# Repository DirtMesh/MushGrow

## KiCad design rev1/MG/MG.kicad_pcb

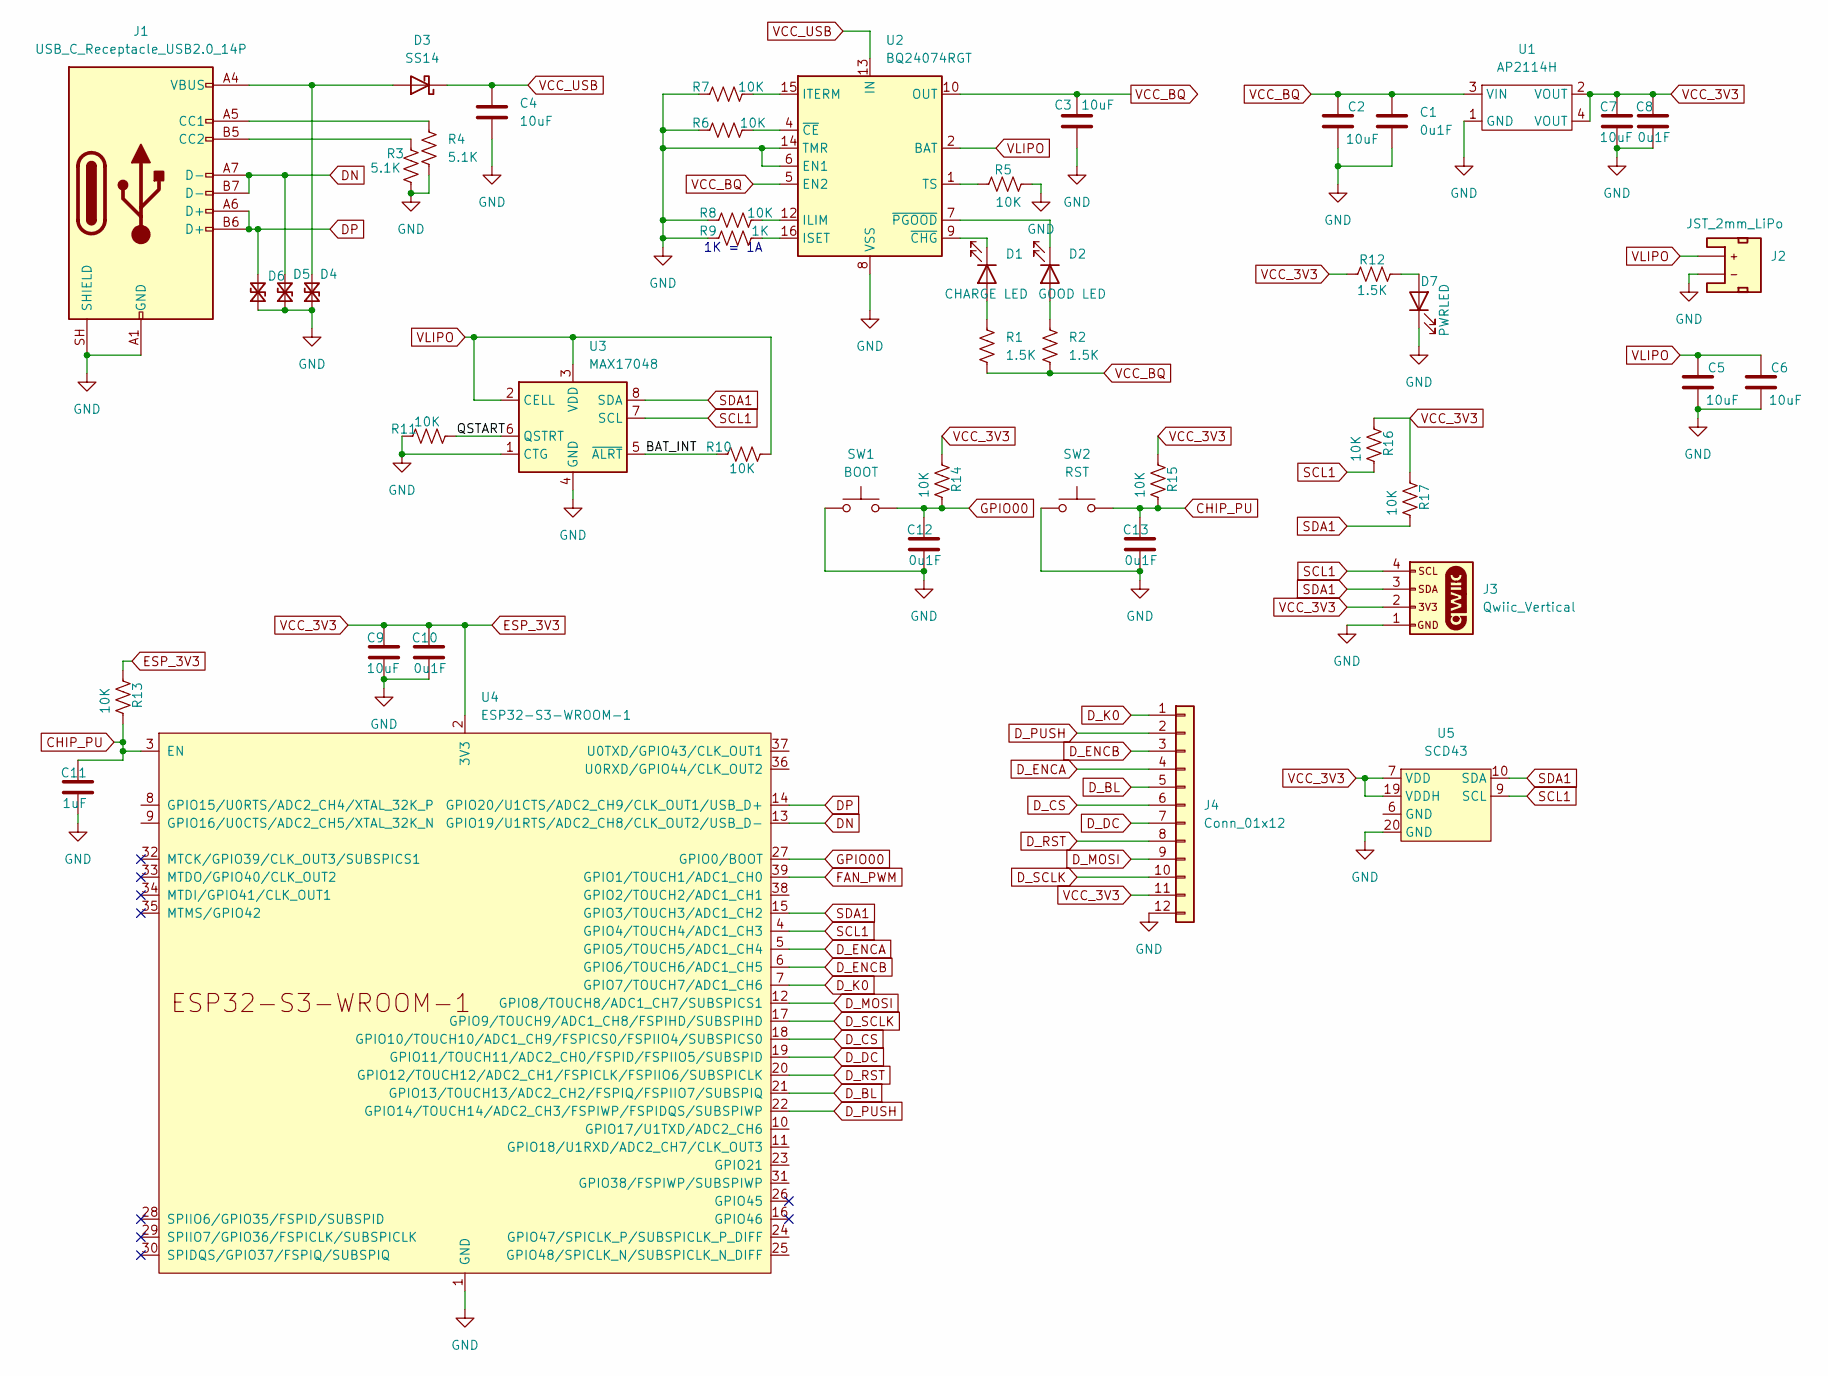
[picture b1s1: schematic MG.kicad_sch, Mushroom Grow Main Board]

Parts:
C1, C8, C10, C12, C13: 0u1F; C_0603_1608Metric
C2, C3, C4, C5, C6, C7, C9: 10uF; C_1206_3216Metric
C11: 1uF; C_0603_1608Metric
D1: CHARGE LED; LED_0603_1608Metric
D2: GOOD LED; LED_0603_1608Metric
D3: SS14; D_SMA
D4, D5, D6: TPD1E10B06DYAR; D_SOD-523
D7: PWRLED; LED_0603_1608Metric
J1: USB_C_Receptacle_USB2.0_14P; USB_C_Receptacle_GCT_USB4085
J2: JST_2mm_LiPo; JST_1x02_P2.0mm_Horizontal_SMD
J3: Qwiic_Vertical; JST_1x04_P1.0mm_Vertical_SMD
J4: Conn_01x12; JST_1x12_P1.0mm_Horizontal_SMD
R1, R2, R12: 1.5K; R_0603_1608Metric
R3, R4: 5.1K; R_0603_1608Metric
R5, R6, R7, R8, R10, R11, R13, R14, R15, R16, R17: 10K; R_0603_1608Metric
R9: 1K; R_0603_1608Metric
SW1: BOOT; Push_SMD_4.6x2.8mm_h1.9mm
SW2: RST; Push_SMD_4.6x2.8mm_h1.9mm
U1: AP2114H; SOT-223
U2: BQ24074RGT; VQFN-16-1EP_3x3mm_P0.5mm_EP1.6x1.6mm
U3: MAX17048; DFN-8_2x2mm_P0.5mm_EP1.2x0.8mm
U4: ESP32-S3-WROOM-1
U5: SCD43; Sensirion_SCD4x-1EP_10.1x10.1mm_P1.25mm_EP4.8x4.8mm

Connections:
/BAT_INT: R10.1, U3.5 (~ALRT)
/QSTART: R11.2, U3.6 (QSTRT)
CHIP_PU: C11.1, C13.1, R13.2, R15.2, SW2.2, U4.3 (EN)
DN: D5.2 (A2), J1.A7 (D-), J1.B7 (D-), U4.13 (GPIO19/U1RTS/ADC2_CH8/CLK_OUT2/USB_D-)
DP: D6.2 (A2), J1.A6 (D+), J1.B6 (D+), U4.14 (GPIO20/U1CTS/ADC2_CH9/CLK_OUT1/USB_D+)
D_BL: J4.5, U4.21 (GPIO13/TOUCH13/ADC2_CH2/FSPIQ/FSPIIO7/S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)
D_CS: J4.6, U4.18 (GPIO10/TOUCH10/ADC1_CH9/FSPICS0/FSPIIO4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)
D_DC: J4.7, U4.19 (GPIO11/TOUCH11/ADC2_CH0/FSPID/FSPIIO5/S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)
D_ENCA: J4.4, U4.5 (GPIO5/TOUCH5/ADC1_CH4)
D_ENCB: J4.3, U4.6 (GPIO6/TOUCH6/ADC1_CH5)
D_K0: J4.1, U4.7 (GPIO7/TOUCH7/ADC1_CH6)
D_MOSI: J4.9, U4.12 (GPIO8/TOUCH8/ADC1_CH7/SUBSPICS1)
D_PUSH: J4.2, U4.22 (GPIO14/TOUCH14/ADC2_CH3/FSPIWP/FSPIDQS/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)
D_RST: J4.8, U4.20 (GPIO12/TOUCH12/ADC2_CH1/FSPICLK/FSPIIO6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)
D_SCLK: J4.10, U4.17 (GPIO9/TOUCH9/ADC1_CH8/FSPIHD/SUBSPIHD)
ESP_3V3: C7.1, C8.1, C9.1, C10.1, J3.2, J4.11, R12.1, R13.1, R14.1, R15.1, R16.1, R17.1, U1.2 (VOUT), U1.4 (VOUT), U4.2 (3V3), U5.7 (VDD), U5.19 (VDDH)
FAN_PWM: U4.39 (GPIO1/TOUCH1/ADC1_CH0)
GND: C1.2, C2.2, C3.2, C4.2, C5.2, C6.2, C7.2, C8.2, C9.2, C10.2, C11.2, C12.2, C13.2, D4.1 (A1), D5.1 (A1), D6.1 (A1), D7.1 (K), J1.A1 (GND), J1.A12 (GND), J1.B1 (GND), J1.B12 (GND), J1.SH (SHIELD), J2.1 (-), J3.1, J4.12, R3.2, R4.2, R5.2, R6.1, R7.1, R8.1, R9.1, R11.1, SW1.1, SW2.1, U1.1 (GND), U2.6 (EN1), U2.8 (VSS), U2.14 (TMR), U2.17 (VSS), U3.1 (CTG), U3.4 (GND), U3.9 (GND), U4.1 (GND), U4.40 (GND), U4.41 (GND), U5.20 (GND)
GPIO00: C12.1, R14.2, SW1.2, U4.27 (GPIO0/BOOT)
unnamed: D1.2 (A), R1.1
unnamed: D1.1 (K), U2.9 (~CHG)
unnamed: D2.2 (A), R2.1
unnamed: D2.1 (K), U2.7 (~PGOOD)
unnamed: D3.2 (A), D4.2 (A2), J1.A4 (VBUS), J1.A9 (VBUS), J1.B4 (VBUS), J1.B9 (VBUS)
unnamed: D7.2 (A), R12.2
unnamed: J1.A5 (CC1), R4.1
unnamed: J1.B5 (CC2), R3.1
unnamed: R8.2, U2.12 (ILIM)
unnamed: R9.2, U2.16 (ISET)
unnamed: R7.2, U2.15 (ITERM)
unnamed: R5.1, U2.1 (TS)
unnamed: R6.2, U2.4 (~CE)
SCL1: J3.4, R16.2, U3.7 (SCL), U4.4 (GPIO4/TOUCH4/ADC1_CH3), U5.9 (SCL)
SDA1: J3.3, R17.2, U3.8 (SDA), U4.15 (GPIO3/TOUCH3/ADC1_CH2), U5.10 (SDA)
VCC_BQ: C1.1, C2.1, C3.1, R1.2, R2.2, U1.3 (VIN), U2.5 (EN2), U2.10 (OUT), U2.11 (OUT)
VCC_USB: C4.1, D3.1 (K), U2.13 (IN)
VLIPO: C5.1, C6.1, J2.2 (+), R10.2, U2.2 (BAT), U2.3 (BAT), U3.2 (CELL), U3.3 (VDD)

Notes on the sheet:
1K = 1A

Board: 2 copper layers, 48 parts (0 on the bottom side), 36 nets, no tracks yet.
